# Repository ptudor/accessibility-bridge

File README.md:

# Accessibility Bridge

Accessibility Bridge lets you operate a second computer with a keyboard and mouse controlled from the command line. You can replay a keyboard-only interaction, check how a dialog handles focus, or repeat a pointer gesture at the same screen coordinates. The target uses its built-in USB HID drivers. All operator software runs on the control computer.

```text
CONTROL computer                                  TARGET computer
hidbridgectl → USB UART → digital isolator → Pico H → USB HID
                        ← replies and CTS#
```

The Pico presents a boot keyboard, a relative mouse, an absolute pointer, and consumer controls. The two computers power their respective sides of the isolator. To see the target display from CONTROL, connect a separate video capture device or encoder. [Display capture guide](docs/CAPTURE.md)

## Try it without hardware

On macOS or Linux, install Go 1.26 or newer and Make. From the repository root, build the controller and start the simulator.

```sh
make host
host/bin/hidbridge-sim
```

In a second terminal at the repository root, set `PORT` to the device path printed by the simulator. On Linux it usually looks like `/dev/pts/3`. Each invocation below opens a fresh session.

```sh
PORT=/dev/pts/3
host/bin/hidbridgectl -port "$PORT" -json status
host/bin/hidbridgectl -port "$PORT" run host/examples/text-selection.hid
```

The status includes `"usb": "configured"` and an identity ending in `SIMULATED`. Watch the simulator terminal for the individual key presses and releases. The example types “Accessibility Bridge” and selects the final letter. With a physical board, open a blank text document on the target first.

## Build a bridge

| What you need | Where to start |
| --- | --- |
| Carrier, cable, and parts | [KiCad project, BOM, wiring, and first power-up](hardware/README.md) |
| Image for the Pico H | [Build and flash the TARGET firmware](firmware/README.md) |
| Commands and scripts for CONTROL | [Controller and simulator](host/README.md) |
| An implementation in another language | [Serial protocol v1](docs/PROTOCOL.md) |

The R1 carrier has passed KiCad electrical, layout, and schematic-parity checks. Physical assembly and bench qualification of this reference layout are pending. The firmware builds for the original RP2040 Pico H. Its default USB identity is the shared private-test pair `1209:0001`. This project has no assigned PID. [USB identity and release status](docs/USB-IDENTITY.md)

## Verification

```sh
make test            # Go race tests, CLI integration, native C tests, C/Go comparison
make hardware-check  # KiCad 10 electrical and design rules, including schematic parity
```

The native tests exercise HID descriptors, report delivery, retries, queue backpressure, bus events, and release after a lost control link. Hardware bring-up also requires observing actual input and measuring current on each USB port. [Bench procedure](hardware/README.md#first-power-up)

Original software is MIT licensed. The reference hardware is licensed under CERN-OHL-P-2.0. [License](LICENSE) · [Third-party notices](THIRD_PARTY.md)

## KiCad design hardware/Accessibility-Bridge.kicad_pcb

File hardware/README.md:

# R1 reference carrier

The carrier joins a Raspberry Pi Pico H to a 3.3 V USB UART through a TI ISO6731DWR. The target computer powers the Pico through its micro-USB port. The control cable powers the other side of the isolator. Three channels cross the barrier for commands, replies, and CTS# flow control. The two grounds have separate copper on both layers.

Open **Accessibility-Bridge.kicad_pro** in KiCad 10 with the standard footprint and 3D model libraries installed. The editable schematic, routed PCB, project symbols, custom footprints, and four part-specific STEP models are included. The board measures 58 × 56.5 mm and uses a 1.6 mm, two-layer stack. A design rule enforces 6 mm clearance between the two named domains. [KiCad project](Accessibility-Bridge.kicad_pro) · [Schematic](Accessibility-Bridge.kicad_sch) · [PCB](Accessibility-Bridge.kicad_pcb)

## Parts for one bridge

| Position | Qty | Manufacturer and part | Function |
| --- | ---: | --- | --- |
| U1 | 1 | Texas Instruments ISO6731DWR | SOIC-16 wide, two forward channels and one reverse, default-high outputs |
| U2 | 1 | Raspberry Pi Pico H, SC0917 | Original non-wireless RP2040 module with soldered headers |
| U2 sockets | 2 | Samtec SSW-120-01-G-S | 1 × 20, 2.54 mm pitch, 8.51 mm body height |
| J1 | 1 | JST B5B-XH-A(LF)(SN) | Keyed vertical five-position XH header, 2.50 mm pitch |
| C1, C2 | 2 | Yageo CC0805KRX7R9BB104 | 100 nF X7R, 0805, one per isolator supply |
| R1, R2 | 2 | Uni-Royal 0805W8F1002T5E | 10 kΩ, 1%, idle pull-ups on TARGET TX and RTS# |
| R3 | 1 | Uni-Royal 0805W8F1001T5E | 1 kΩ, 1%, HELD LED current limit |
| D1 | 1 | Everlight 17-21SURC/S530-A3/4T | Red 0805 indicator, cathode to pad 1 |
| CONTROL cable | 1 | FTDI TTL-232RG-VREG3V3-WE | USB-A to wire ends, regulated 3.3 V supply and 3.3 V UART with CTS# |
| Cable housing and contacts | 1 + 5 | JST XHP-5 and SXH-001T-P0.6 | Crimp to the five used cable conductors |
| TARGET cable | 1 | USB data cable with a micro-B plug | Connects the Pico to the target |

The Pico H supplies the flash, crystal, regulator, USB connector, BOOTSEL button, and green LINK LED. Its plug-in sockets are 17.78 mm apart. The board also has four unplated 2.7 mm mounting holes. [Pico module drawing and pinout](https://datasheets.raspberrypi.com/pico/pico-datasheet.pdf) · [Socket drawing](https://www.samtec.com/products/ssw-120-01-g-s)

## Wire the CONTROL connector

Pin numbers refer to **J1 on the PCB**. Pin 1 has a square copper pad. Match the housing cavity numbers before crimping. RXD, TXD, and CTS# below are named from the cable's point of view.

| J1 | Cable wire | Connection |
| ---: | --- | --- |
| 1 | Red, VCC | Regulated 3.3 V to U1 VCC2 and EN2 |
| 2 | Black, GND | CONTROL ground |
| 3 | Yellow, RXD | Replies from Pico GP0 through U1 channel A |
| 4 | Brown, CTS# | Receive permission from Pico GP3 through U1 channel B |
| 5 | Orange, TXD | Commands to Pico GP1 through U1 channel C |

Insulate the spare green RTS# wire. Check for 3.3 V between J1 pins 1 and 2 on the cable **before mating it**. Similar FTDI cables can have 3.3 V logic and a 5 V power lead. The specified cable supplies 3.3 V on both. [FTDI cable datasheet, section 4](https://ftdichip.com/wp-content/uploads/2023/07/DS_TTL-232RG_CABLES.pdf) · [JST XH drawing](https://www.jst-mfg.com/product/pdf/eng/eXH.pdf)

U1 side 1 faces the Pico. Target TX, RTS#, and RX connect to U1 pins 3, 4, and 5 respectively. U1 pins 14, 13, and 12 face J1. Each enable is tied to its local 3.3 V supply. With TARGET unpowered, the default-high isolator output deasserts the cable's CTS#. The default-high part and a cable with hardware flow control are essential to this behavior. [TI ISO6731 datasheet, pin functions and device functional modes](https://www.ti.com/lit/ds/symlink/iso6731.pdf)

## First power-up

1. With both cables disconnected, orient U1 by the pin-1 mark and D1 by its cathode. Solder the passives, J1, and the two parallel Pico sockets. Fit the Pico H with GP0 at square pad 1 and its USB connector at that end of the carrier.
2. Check that each supply is free of shorts to its own ground and that CONTROL and TARGET ground have no DC continuity. Connect CONTROL alone. Measure about 3.3 V across C1 and an unpowered rail across C2. Disconnect CONTROL and repeat with TARGET only. C2 should now be powered and C1 unpowered.
3. Flash the Pico and connect it to the target. The green LED should light after USB configuration. Connect CONTROL and run `hidbridgectl -port "$PORT" status`. Expect firmware 0.2, a configured USB device, and no held inputs. [Flashing instructions](../firmware/README.md)
4. Start with Caps Lock off and run the keyboard LED check. Open a blank document on the target and run the text-selection example. Check each physical effect against its session transcript. [Controller examples](../host/examples/)
5. For loss-of-link testing, hold Shift in an interactive `run -` session and unplug CONTROL while TARGET stays powered. HELD should extinguish after the 500 ms watchdog interval and the target should release Shift. Reconnect, read the watchdog count, and check that typing has returned to normal.

This layout awaits physical verification of harness fit, signal timing at 1 Mbaud, watchdog release, and active and suspend current. Connectors, debug leads, and test equipment can provide an external ground path. The board is designed for two USB-powered computer interfaces and has no system-level electrical safety certification.

## Check and export

```sh
make -C hardware check
make -C hardware fabrication
```

Run these commands at the repository root with KiCad 10, Make, and Python 3 on your path. The checks refill the ground zones, compare the PCB with the schematic, and verify the firmware GPIOs and cable pinout against the exported nets. Manufacturing plots and separate plated and non-plated drills go into `hardware/dist/gerbers/`. [3D model provenance](models/README.md)

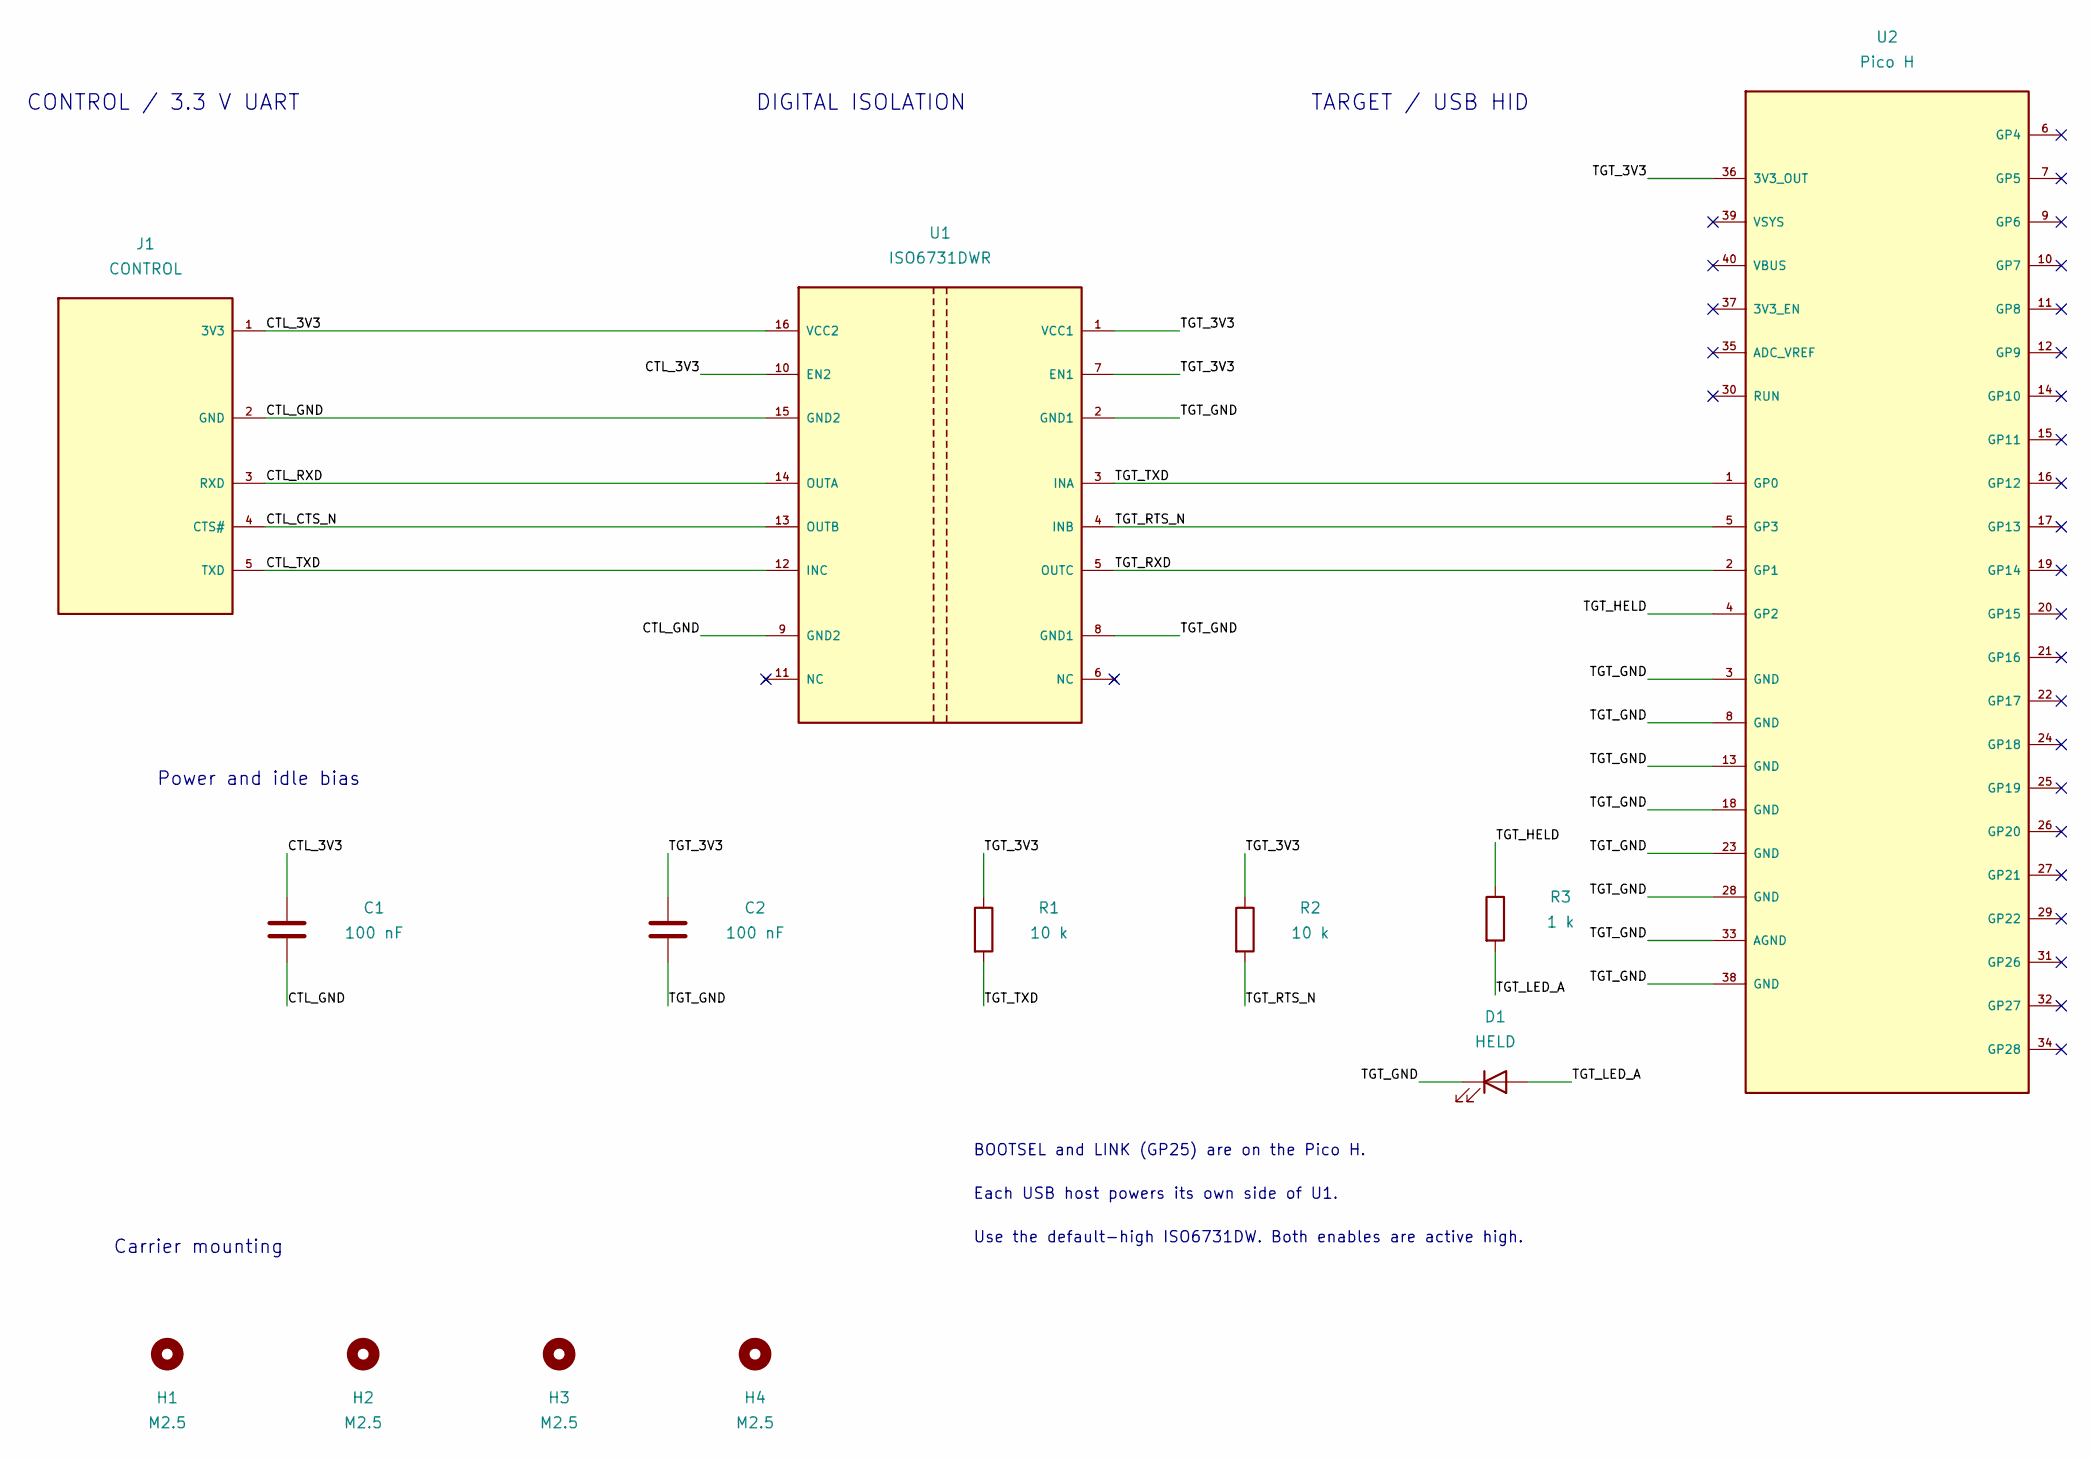
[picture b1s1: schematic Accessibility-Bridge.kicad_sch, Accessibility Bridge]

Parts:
C1, C2: 100 nF; CC0805KRX7R9BB104; MPN CC0805KRX7R9BB104
D1: HELD; LED_0805_2012Metric; MPN 17-21SURC/S530-A3/4T
H1, H2, H3, H4: M2.5; MountingHole_2.7mm_M2.5
J1: CONTROL; JST_XH_B5B-XH-A_1x05_P2.50mm_Vertical; MPN B5B-XH-A(LF)(SN)
R1, R2: 10 k; 0805W8F1002T5E; MPN 0805W8F1002T5E
R3: 1 k; 0805W8F1001T5E; MPN 0805W8F1001T5E
U1: ISO6731DWR; ISO6731_DW; MPN ISO6731DWR
U2: Pico H; Pico_H_Socket; MPN SC0917

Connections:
/CTL_3V3: C1.1, J1.1 (3V3), U1.10 (EN2), U1.16 (VCC2)
/CTL_CTS_N: J1.4 (CTS#), U1.13 (OUTB)
/CTL_GND: C1.2, J1.2 (GND), U1.9 (GND2), U1.15 (GND2)
/CTL_RXD: J1.3 (RXD), U1.14 (OUTA)
/CTL_TXD: J1.5 (TXD), U1.12 (INC)
/TGT_3V3: C2.1, R1.1, R2.1, U1.1 (VCC1), U1.7 (EN1), U2.36 (3V3_OUT)
/TGT_GND: C2.2, D1.1 (K), U1.2 (GND1), U1.8 (GND1), U2.3 (GND), U2.8 (GND), U2.13 (GND), U2.18 (GND), U2.23 (GND), U2.28 (GND), U2.33 (AGND), U2.38 (GND)
/TGT_HELD: R3.1, U2.4 (GP2)
/TGT_LED_A: D1.2 (A), R3.2
/TGT_RTS_N: R2.2, U1.4 (INB), U2.5 (GP3)
/TGT_RXD: U1.5 (OUTC), U2.2 (GP1)
/TGT_TXD: R1.2, U1.3 (INA), U2.1 (GP0)

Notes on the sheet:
BOOTSEL and LINK (GP25) are on the Pico H.
CONTROL / 3.3 V UART
DIGITAL ISOLATION
Power and idle bias
TARGET / USB HID
Each USB host powers its own side of U1.
Use the default-high ISO6731DW. Both enables are active high.
Carrier mounting

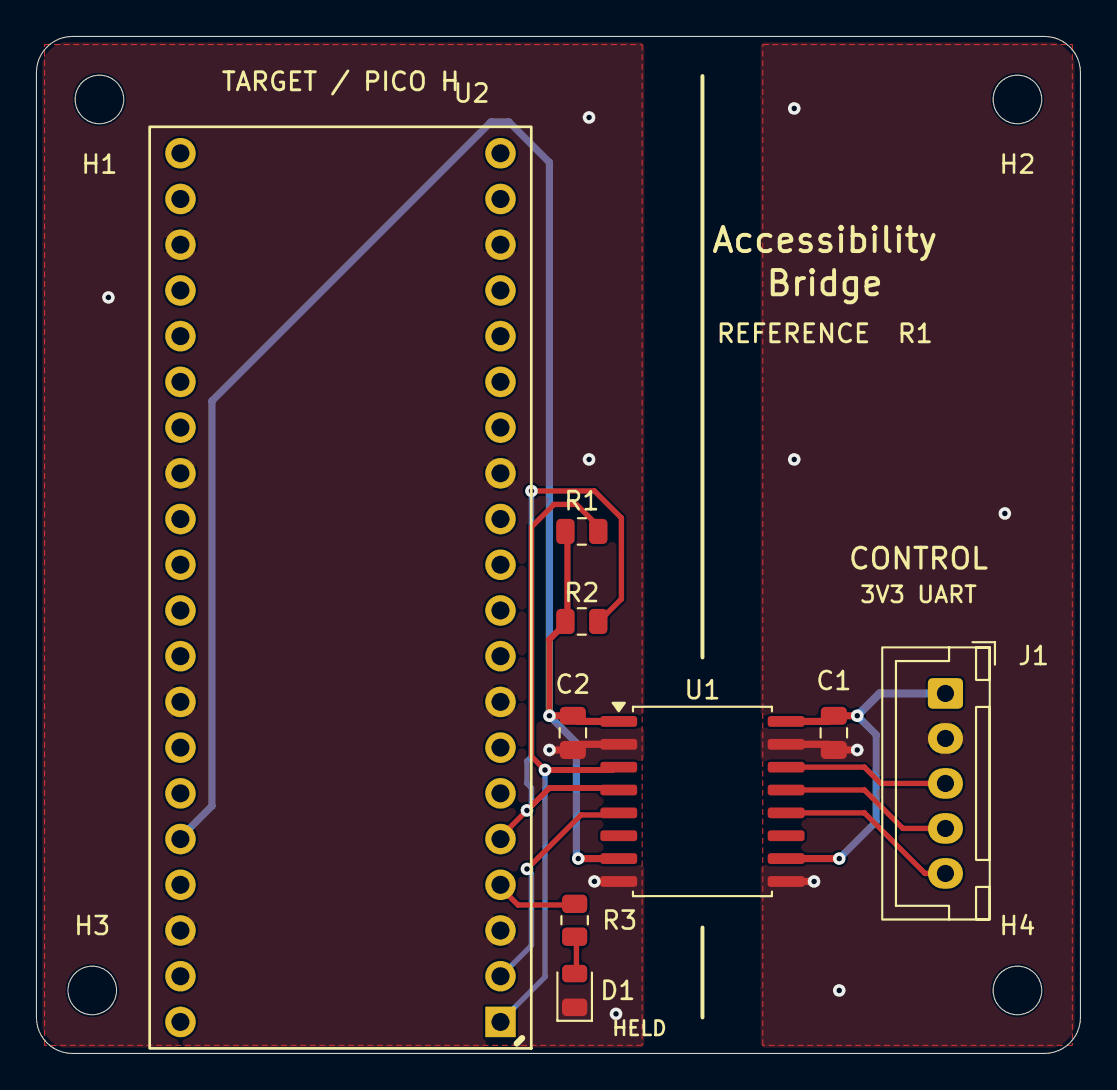
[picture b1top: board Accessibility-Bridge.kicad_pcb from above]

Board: 2 copper layers, 58.0 x 56.5 mm, 13 parts (0 on the bottom side), 12 nets.
